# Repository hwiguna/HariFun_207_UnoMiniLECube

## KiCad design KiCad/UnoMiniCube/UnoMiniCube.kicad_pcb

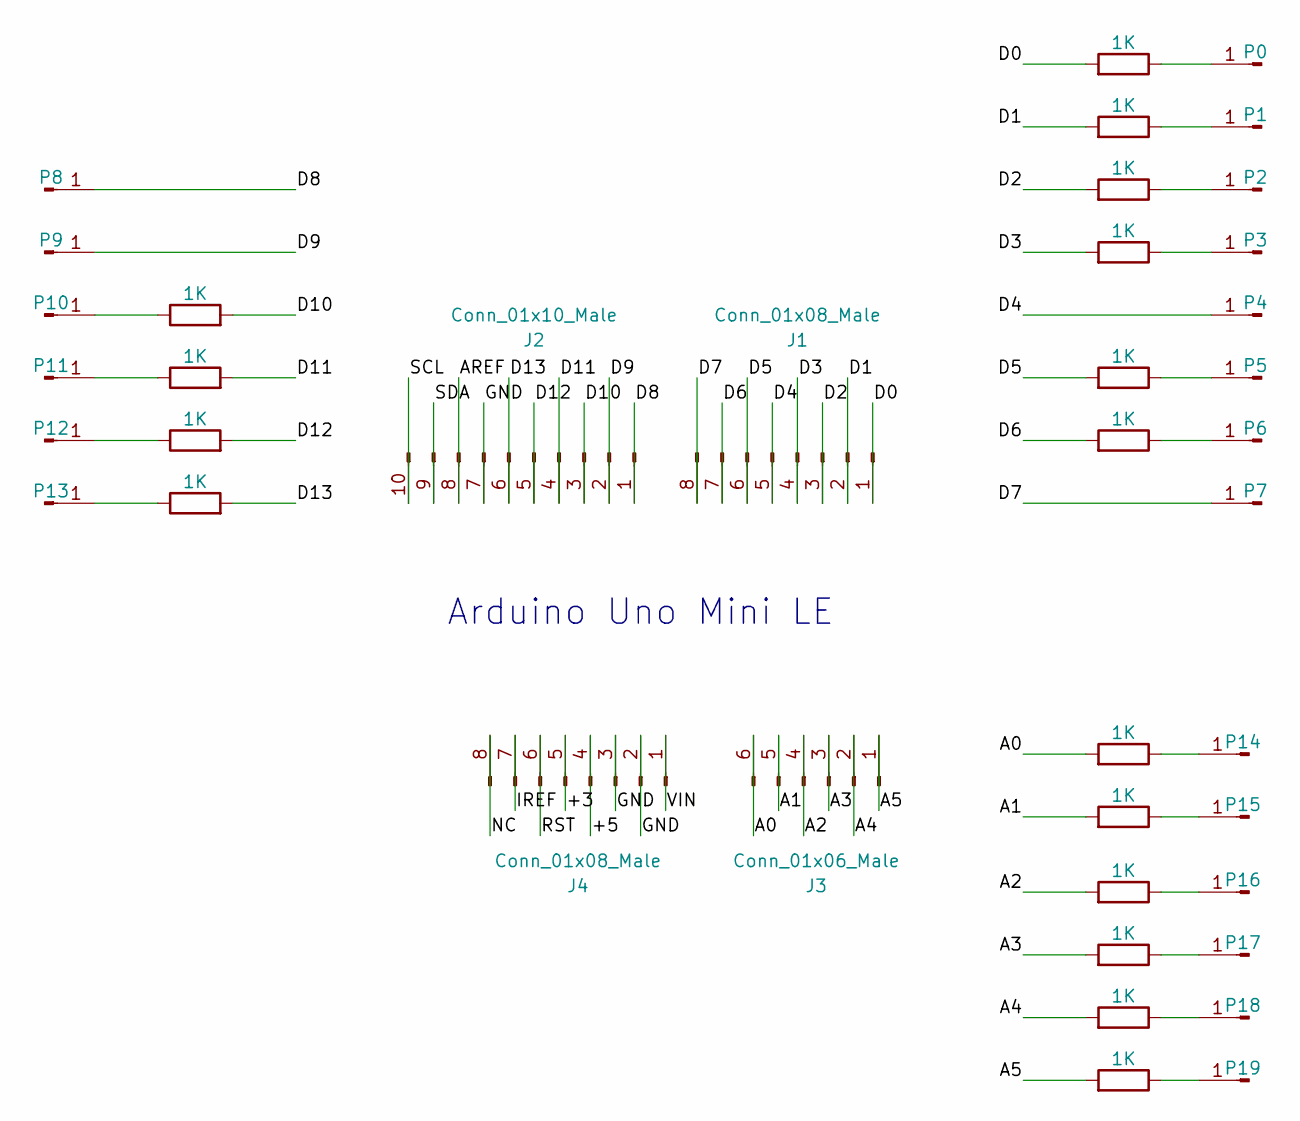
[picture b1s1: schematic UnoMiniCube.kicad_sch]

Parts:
J1, J4: Conn_01x08_Male; PinHeader_1x08_P1.27mm_Vertical
J2: Conn_01x10_Male; PinHeader_1x10_P1.27mm_Vertical
J3: Conn_01x06_Male; PinHeader_1x06_P1.27mm_Vertical
P0, P1, P2, P3, P4, P5, P6, P7, P8, P9, P10, P11, P12, P13, P14, P15, P16, P17, P18, P19: Conn_01x01_Male; PinHeader_1x01_P1.27mm_Vertical_Hari
R1, R2, R3, R4, R5, R6, R7, R11, R12, R13, R14, R15, R16, R17, R18, R19: 1K; R_0805_2012Metric_Pad1.20x1.40mm_HandSolder

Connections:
/+3: J4.5
/+5: J4.4
/A0: J3.6, R19.2
/A1: J3.5, R18.2
/A2: J3.4, R17.2
/A3: J3.3, R5.2
/A4: J3.2, R16.2
/A5: J3.1, R15.2
/AREF: J2.8
/D0: J1.1, R1.2
/D1: J1.2, R2.2
/D2: J1.3, R3.2
/D3: J1.4, R4.2
/D4: J1.5, P4.1
/D5: J1.6, R6.2
/D6: J1.7, R7.2
/D7: J1.8, P7.1
/D8: J2.1, P8.1
/D9: J2.2, P9.1
/D10: J2.3, R11.2
/D11: J2.4, R12.2
/D12: J2.5, R13.2
/D13: J2.6, R14.2
/GND: J2.7, J4.2, J4.3
/IREF: J4.7
/NC: J4.8
/RST: J4.6
/SCL: J2.10
/SDA: J2.9
/VIN: J4.1
unnamed: P0.1, R1.1
unnamed: P1.1, R2.1
unnamed: P2.1, R3.1
unnamed: P3.1, R4.1
unnamed: P5.1, R6.1
unnamed: P6.1, R7.1
unnamed: P10.1, R11.1
unnamed: P11.1, R12.1
unnamed: P12.1, R13.1
unnamed: P13.1, R14.1
unnamed: P14.1, R19.1
unnamed: P15.1, R18.1
unnamed: P16.1, R17.1
unnamed: P17.1, R5.1
unnamed: P18.1, R16.1
unnamed: P19.1, R15.1

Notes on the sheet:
Arduino Uno Mini LE

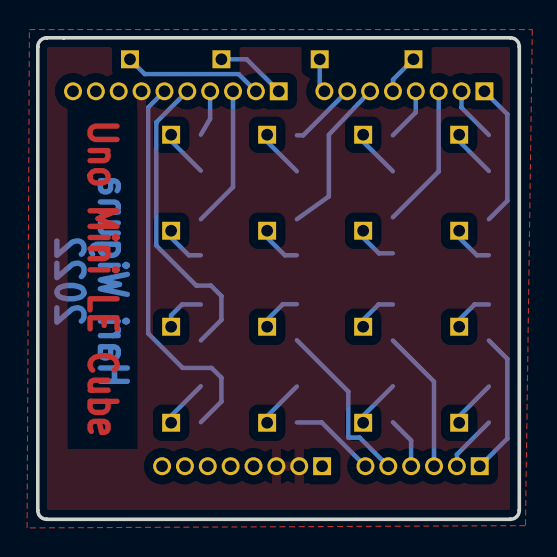
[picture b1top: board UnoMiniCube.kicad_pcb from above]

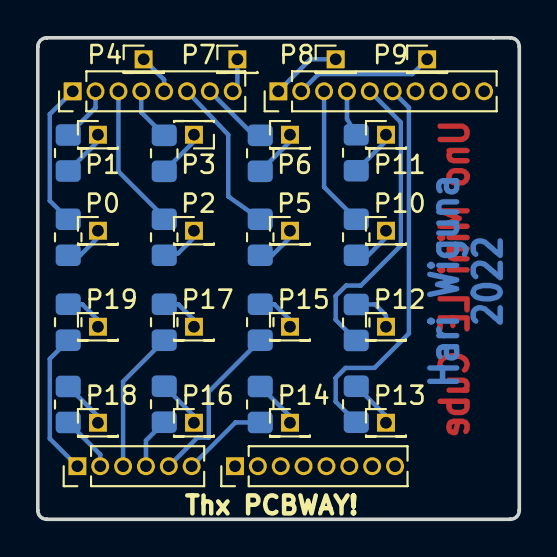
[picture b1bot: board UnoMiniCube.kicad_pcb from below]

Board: 2 copper layers, 26.8 x 26.8 mm, 40 parts (40 on the bottom side), 37 nets.

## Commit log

2022-05-30 Implement showing text
2022-05-30 Cleanup VS temp files
2022-05-30 Tell gitignore to ignore everything in the .vs dir
2022-05-30 Implemented Raise and Lower Cube
2022-05-30 Major code cleanup. Still have to fix plane vs orientation.
2022-05-31 Convert orientation and plane into just along which axis is considered the depth.
2022-05-31 Push notes and script
2022-06-09 Change the "front" of the cube
2022-06-09 Commit gerbers
2022-06-18 Got the hat working!
2022-06-20 Moar effects!
2022-06-22 Started atom class
2022-06-26 Atom class is working, but I think it is actually harder to use than just doing loops. So I will commit this and rewrite the atom effect without classes.
2022-06-26 We better stop making effects and finish the video!
